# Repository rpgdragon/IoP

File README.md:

# Aplicación Móvil IoP-Shirt

Antes de utilizar el presente producto debe hacerse con una camiseta inteligente diseñada especificamente para este proyecto..

Antes de realizar cualquier compilación, es necesario que el entorno tenga instaladas las siguientes herramientas
- Node (con npm, actualmente, 10.16.0)
- NPM 6.9.0
- Agregar gradle versión 5.5.* al path del sistema.
- En caso de que ocurra un error relacionado con memoria en la ejecución de gradle, agregar la variable _JAVA_OPTIONS al sistema con el valor -Xmx512M -Xms512M
- Hacer un npm install en la raiz del proyecto de Webapp

- Si da un error de Duplicate Classes hay que añadir en el gradle.properties las siguientes propiedades.

android.enableJetifier=true
android.useAndroidX=true

Todos los procesos indicados aquí son para ser probados en un dispositivo con sistema operativo Android. Las instrucciones para instalarlos en IOS estarán proximamente.

## Android

### Compilar
Para compilar la aplicación y generar una APK para probar la aplicación debe en un entorno se debe utilizar el comando npm

npm run build-android-@entorno@

Donde @entorno@ puede ser los siguientes valores:

- dev:		 Entorno de desarrollo, pruebas en el móvil
- prod:		 Entorno en producción, se firma la APK como release como si fuera la aplicación a descargarse en Google Play. Esta APK no sirve para subirla a Google Play

Si no se indica nada y se indica solamente:

npm run build-android

Se generará la versión para el entorno de dev.

### Compilar y ejecutar
Para compilar la versión y ejecutarla en un dispositivo móvil debe utilizar el comando nmp

npm run build-run-android-@entorno@

Donde @entorno@ puede ser los siguientes valores:

- dev:		 Entorno de desarrollo, pruebas en el móvil
- prod:		 Entorno en producción, se firma la APK como release como si fuera la aplicación a descargarse en Google Play. Esta APK no sirve para subirla a Google Play

Si no se indica nada y se indica solamente:

npm run build-run-android

Se compilará y ejecutará la versión para el entorno de dev.

### Ejecutar

Para simplemente ejecutar la aplicación recientemente compilada se debe utilizar el comando npm

npm run run-android-@entorno@

Donde @entorno@ puede ser los siguientes valores:

- dev:		 Entorno de desarrollo, pruebas en el móvil
- prod:		 Entorno en producción, se firma la APK como release como si fuera la aplicación a descargarse en Google Play. Esta APK no sirve para subirla a Google Play

Si no se indica nada y se indica solamente:

npm run run-android

Se ejecutará la versión para el entorno de dev.

### Generar versión
Para generar la versión que irá al Google Play se debe utuilizar el comando npm

npm run create-android-version

En el mismo se le pedirá que introduzca la contraseña del almacen de claves para firmar la aplicación. Una vez introducido se firmará y se optimizará la APK que podrá ser subida a Google Play.

##IOS
Proximamente

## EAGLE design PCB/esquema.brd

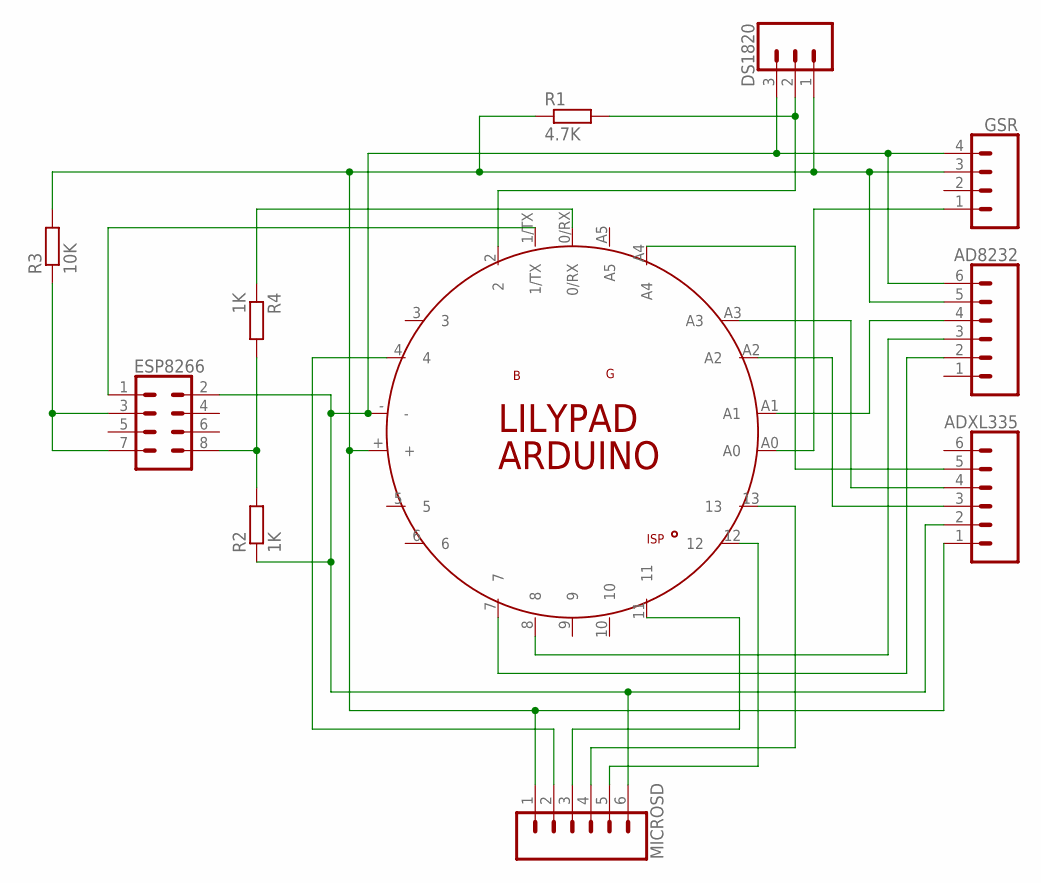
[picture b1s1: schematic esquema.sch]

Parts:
AD8232: CONN_06FEMALE_LOCK; 1X06_FEMALE_LOCK.010
ADXL335: CONN_06FEMALE_LOCK; 1X06_FEMALE_LOCK.010
DS1820: CONN_03; 1X03
ESP8266: CONN_04X2; 2X4
GSR: CONN_04JST-PTH; JST-4-PTH
MICROSD: CONN_06FEMALE_LOCK; 1X06_FEMALE_LOCK.010
PCB1: ARDUINO_LILYPAD
R1: 4.7K; 0309/12
R2, R4: 1K; 0309/12
R3: 10K; 0309/12

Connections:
unnamed: MICROSD.3, PCB1.11
unnamed: MICROSD.2, PCB1.4
unnamed: GSR.1, PCB1.A0
unnamed: AD8232.4, PCB1.A1
unnamed: AD8232.3, PCB1.8
unnamed: AD8232.2, PCB1.7
unnamed: DS1820.2, PCB1.2, R1.2
unnamed: ADXL335.3, PCB1.A2
unnamed: ADXL335.4, PCB1.A3
unnamed: ESP8266.3, ESP8266.7, R3.1
unnamed: ADXL335.5, PCB1.A4
unnamed: ESP8266.1, PCB1.1/TX
unnamed: ESP8266.8, R2.2, R4.2
unnamed: PCB1.0/RX, R4.1
unnamed: AD8232.5, ADXL335.1, DS1820.1, GSR.3, MICROSD.1, PCB1.+, R1.1, R3.2
unnamed: AD8232.6, ADXL335.2, DS1820.3, ESP8266.2, GSR.4, MICROSD.6, PCB1.-, R2.1
unnamed: MICROSD.4, PCB1.13
unnamed: MICROSD.5, PCB1.12

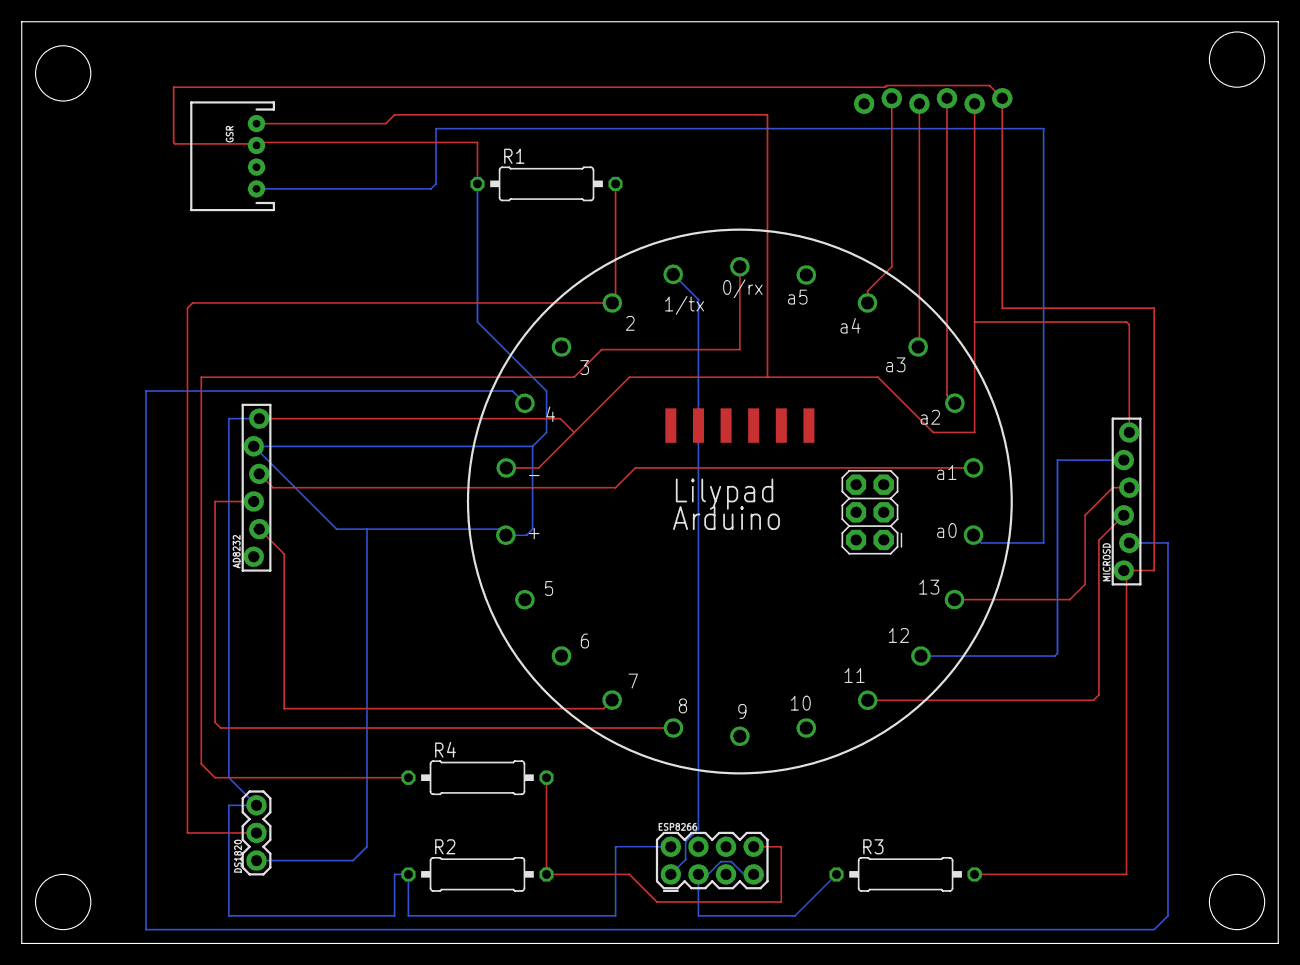
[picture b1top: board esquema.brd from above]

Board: 2 copper layers, 115.5 x 84.8 mm, 11 parts (1 on the bottom side), 18 nets.

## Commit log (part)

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2019-10-06 PEC2 2 Avance
2019-10-07 PEC 2 Avance 3
2019-10-07 Planificacion Gant Avance 1
2019-10-08 Planificacion Gant Avance 2
2019-10-11 PEC avance 3
2019-10-12 PEC2 Avance 4
2019-10-14 Entrega Final PEC2 + Correos
2019-10-14 Cambiado titulo TFM
2019-10-15 Balsamiq Pre Login
2019-10-16 Primera version Constantes
2019-10-17 Fin primeras capturas Balsamiq
2019-10-18 Post Balsamiq Iteracion1
2019-10-18 Capturas Balsamiq post final
2019-10-18 Final Balsamiq Iteracion1
2019-10-20 SplashScreen Ventana
2019-10-20 PaginaMain Avance 1
2019-10-21 Rehecho Estructura proyecto
2019-10-22 Fin Main y Quees
2019-10-22 Fin pantalla Login
2019-10-23 Facebook 50%
2019-10-24 Login Facebook Interface
2019-10-24 Backend Login excepto Facebook
2019-10-24 Proyecto SDK Facebook
2019-10-24 Añadido Provider Rest
2019-10-25 Fin Login No Facebook
2019-10-25 Fin Login No Facebook Backend
2019-10-26 Fin Desarrollo Login
2019-10-27 Publicando Version 0.0.1
2019-10-27 Capturas Balsamiq Sprint 2 Registro
2019-10-27 Cambios Olvidos Contrasena
2019-10-28 Preparando cmabios olvido
2019-10-29 Olvido, solo queda pagina reseteo contraseñas
2019-10-29 Fin Codigo Olvido y Recuperacion
2019-10-30 Correcciones Olvido
2019-10-30 Correcciones Olvido y añadido restricciones seguridad contraseña
2019-10-30 Menu Registro Iniciado
2019-10-31 Casi finalizado Registro no Facebook
2019-10-31 Fin Registro No Facebook
2019-10-31 Scripts Registro
2019-10-31 Registro con Facebook
2019-11-01 Correccion no icono password
2019-11-01 Fin Capturas Balsamiq
2019-11-03 Cambios Lista Camisetas PrePruebas
2019-11-03 Fin Lista Camisetas
2019-11-05 Constantes Vitales Inicios
2019-11-05 Continuacion Calendario
2019-11-06 Cambios Balsamiq Sprint 1
2019-11-07 Avance Ventana constantes, Falta Backend
2019-11-08 Preparacion PEC3
2019-11-08 Iniciando version 0.0.3
2019-11-08 Empieza redacción Memoria
2019-11-08 Corregido Doc abierto
2019-11-10 Preparando PEC3 y Memoria
2019-11-11 Version PEC3
2019-11-11 Arduino GSR
2019-11-13 Haciendo PCB
2019-11-13 Fin PCB
2019-11-13 Capturas Balsamiq Sprint 3
2019-11-14 Eliminando fichero docx
2019-11-14 Balsamiq Sprints 3 y 4
2019-11-14 Primera Versión Listas con Botones Laterales
2019-11-15 Nuevas 4 paginas
2019-11-17 Avances Sprint 3
2019-11-19 Capturas Balsamiq actualizadas
2019-11-19 Avance Backend Datos Camiseta
2019-11-21 Fin Registro Camiseta
2019-11-25 Correcciones Crear Camiseta y Borrado Camiseta
2019-11-25 Añadido SSL en servidor
2019-11-25 Corregido capturas Balsamiq
2019-11-25 Actualizacion Camiseta. Fin versión 0.0.3
2019-11-29 Haciendo generador de codigo
2019-11-29 Fichero scripts
2019-12-03 Subiendo versión con autogeneracion de datos
2019-12-04 Trabajando en la visualizacion constantes vitales
2019-12-05 Fin datos Constantes
2019-12-09 Fin Version 0.0.4
2019-12-22 Version Notificaciones
2019-12-23 Version Notificaciones 1º Beta
2019-12-23 Borrado Fichero que no deberia estar
2019-12-23 Borrado de fichero que no deberia estar
2019-12-28 Iniciando Version 0.0.6
2019-12-29 Funcionalidad campos adicionales
2019-12-31 Entrega antes de que termine el año
2019-12-31 Fin version Sprint 6
2019-12-31 Informe Trabajo
2020-01-20 Entrega final Proyecto UOC
2020-03-05 Version 0.0.7
2020-03-05 Limpieza proyecto
2020-03-06 Renombrando carpetas
2020-03-06 Nombre APP definitiva IoP-Shirt
2020-03-20 Cambios empieza fase 2
2020-03-21 Google Services actualizado
2020-03-21 Cambios nueva app Facebook
2020-03-21 Corregido clearEdit
2020-03-22 Cambios en Iteraciones
2020-03-23 Actualizacion Login Google
2020-03-23 Se queda en Google solo
2020-03-24 Corregido errores login Google
2020-03-27 Actualizado Sprint 7
2020-05-05 Sprints 7 y 8
2020-05-09 Avances Sprint 7 no finalizados
2020-05-10 Correccion iconos
2020-05-16 Fin version creacion Camiseta
2020-05-16 Modificaciones Balsamiq
2020-05-17 Telefono Sprint 8
2020-05-23 Tabs personalizados
2020-05-24 Final implementacion Sprint 8
2020-06-09 Cambios codigo Arduino camiseta 1
2020-06-10 Cambios PCB
2020-06-10 Actualizacion codigo Arduino
2020-06-11 Correcciones
2020-06-12 API Rest envio Informacion
2020-06-16 Cambios Finales PCB
2020-06-17 Primera Versión Codigo Raspberry
2020-06-17 Version con Tratamiento de errores SD
2020-06-19 Cambios 19 de Junio
2020-06-19 Correccion errores iopshirt ionic
2020-06-19 Correcciones subida datos
2020-06-20 Cambios dia 20
2020-06-21 Memoria dia 20 noche
2020-06-22 Actualizado Memoria dia 21 noche
2020-06-22 Avances memoria 22 Junio
2020-06-23 Correcciones en manuales
2020-06-23 Bump https-proxy-agent from 2.2.2 to 2.2.4 in /Codigo/Webapp
    Bumps [https-proxy-agent](https://github.com/TooTallNate/node-https-proxy-agent) from 2.2.2 to 2.2.4.
    - [Release notes](https://github.com/TooTallNate/node-https-proxy-agent/releases)
    - [Commits](https://github.com/TooTallNate/node-https-proxy-agent/compare/2.2.2...2.2.4)
2020-06-23 Bump websocket-extensions from 0.1.3 to 0.1.4 in /Codigo/Webapp
    Bumps [websocket-extensions](https://github.com/faye/websocket-extensions-node) from 0.1.3 to 0.1.4.
    - [Release notes](https://github.com/faye/websocket-extensions-node/releases)
    - [Changelog](https://github.com/faye/websocket-extensions-node/blob/master/CHANGELOG.md)
    - [Commits](https://github.com/faye/websocket-extensions-node/compare/0.1.3...0.1.4)
2020-06-23 Revert "Documentando cambios sprints 80%"
    This reverts commit e01d71ded7b78767608d4121d6d588ba53428f60.
2020-06-23 Documentando cambios Sprints 80%
2020-06-23 Iniciando Sprint 0
2020-06-23 Sprint 0 Avance 1
2020-06-23 Sprint 0 avance 2
2020-06-23 Sprint 0 avance 3
2020-06-23 Sprint 0 avance 4
2020-06-23 Sprint 0 + Correos
2020-06-23 Nombre app provisional Healthshirt
2020-06-23 Preparacion Sprint 3
2020-06-23 Preparando Memoria
2020-06-23 Version documental de memoria
2020-06-23 Informe progresión app movil
2020-06-23 Final de funcionalides básicas app movil
2020-06-23 Update index.html
    Eliminación de clave API
2020-06-23 Camiseta 2222222222222222 como virtual
2020-06-23 Avances 23 de Junio
2020-06-24 Memoria actualizacion 24 junio
2020-06-25 Avances memoria dia 25 junio
2020-06-26 Actualizacion 1 memoria dia 26
2020-06-27 Memoria avances 26 Junio
2020-06-27 Cambios PCB Bluetooth
2020-06-27 Avances dia 27
2020-06-28 Actualizacion memoria dia 28
2020-06-28 Cambios en aplicacion Sprint 7
2020-06-29 Actualizaciones memoria dia 29
2020-07-01 Avances dia 30
2020-07-01 Cambios Backend
2020-07-01 Cambios en Webapp
2020-07-03 Primera version final prefaltas
2020-07-03 Memoria Final
2020-07-03 Cambios Finales Raspberry
2020-07-03 Version final IopShirt
2020-07-03 Actualizado anexoD
2020-07-08 Correcciones y presentacion
2020-07-08 Error fichero docx
2020-07-10 Presentacion final
2021-01-06 Bump axios from 0.19.2 to 0.21.1 in /Codigo/Raspberry/web
    Bumps [axios](https://github.com/axios/axios) from 0.19.2 to 0.21.1.
    - [Release notes](https://github.com/axios/axios/releases)
    - [Changelog](https://github.com/axios/axios/blob/v0.21.1/CHANGELOG.md)
    - [Commits](https://github.com/axios/axios/compare/v0.19.2...v0.21.1)
2021-03-10 Bump elliptic from 6.4.1 to 6.5.4 in /Codigo/Webapp
    Bumps [elliptic](https://github.com/indutny/elliptic) from 6.4.1 to 6.5.4.
    - [Release notes](https://github.com/indutny/elliptic/releases)
    - [Commits](https://github.com/indutny/elliptic/compare/v6.4.1...v6.5.4)
2021-04-01 Bump y18n from 3.2.1 to 3.2.2 in /Codigo/Webapp
    Bumps [y18n](https://github.com/yargs/y18n) from 3.2.1 to 3.2.2.
    - [Release notes](https://github.com/yargs/y18n/releases)
    - [Changelog](https://github.com/yargs/y18n/blob/master/CHANGELOG.md)
    - [Commits](https://github.com/yargs/y18n/commits)
2021-05-11 Bump hosted-git-info from 2.7.1 to 2.8.9 in /Codigo/Webapp
    Bumps [hosted-git-info](https://github.com/npm/hosted-git-info) from 2.7.1 to 2.8.9.
    - [Release notes](https://github.com/npm/hosted-git-info/releases)
    - [Changelog](https://github.com/npm/hosted-git-info/blob/v2.8.9/CHANGELOG.md)
    - [Commits](https://github.com/npm/hosted-git-info/compare/v2.7.1...v2.8.9)

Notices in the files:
parts and their libraries:
SparkFun-Connectors: Licensing: Creative Commons ShareAlike 4.0 International - https://creativecommons.org/licenses/by-sa/4.0
